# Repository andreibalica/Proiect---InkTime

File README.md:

# InkTime Smartwatch - Documentatie Hardware

Acest repository contine fisierele de proiectare hardware (scheme electronice, layout PCB) pentru InkTime, un smartwatch open-source. Proiectul este axat pe eficientizarea consumului energetic si integrarea unui afisaj bi-stabil.

## 1. Principiu de Functionare si Eficienta Energetica

Sistemul elimina limitarile de autonomie specifice smartwatch-urilor clasice prin utilizarea unui ecran tip E-Paper (electroforetic). 

Datorita proprietatii de bi-stabilitate, matricea display-ului isi pastreaza starea fara a necesita alimentare continua. Consumul de energie are loc exclusiv pe durata ciclului de refresh (schimbarea informatiei afisate). Aceasta caracteristica tehnica permite microcontroller-ului sa ramana in modul "Deep Sleep" pe perioade lungi, asigurand o autonomie extinsa si eliminand totodata necesitatea iluminarii de fundal (Backlight).

## 2. Subsisteme Componente

Arhitectura sistemului este impartita in urmatoarele blocuri functionale majore:

* **Microcontroller (MCU):** Implementat in jurul SoC-ului nRF52840 (Nordic Semiconductor). Ofera suport nativ pentru protocolul Bluetooth 5.0 (BLE) si asigura procesarea generala, gestionand atat magistralele de date, cat si modurile de operare ultra-low power.
* **Power Management Unit (PMU):**
  * **Circuit de Incarcare:** Controller dedicat pe portul USB-C, echipat cu protectie la supratensiune si descarcari electrostatice (ESD / diode TVS).
  * **Regulator DC/DC:** Ofera o tensiune stabilizata de 3.3V necesara liniilor digitale, compensand variatiile de tensiune ale acumulatorului LiPo.
  * **Fuel Gauge:** Integrat de masurare a capacitatii reziduale (State of Charge). Citeste datele celulei LiPo fara a necesita un rezistor de shunt si raporteaza valorile prin I2C.
* **Senzoristica si Interfata Utilizator:**
  * **IMU (Inertial Measurement Unit):** Senzor accelerometric utilizat pentru numararea pasilor si detectia gestului de activare a ecranului.
  * **Driver Haptic:** Asigura comanda prin PWM a motorului de vibratii pentru generarea alertelor tactile.
  * **Input Hardware:** Trei butoane mecanice conectate pe porturile GPIO pentru operarea dispozitivului.

## 3. Interfete de Comunicatie

Comunicatia in interiorul sistemului este structurata pentru a separa transferul de date rapid de citirea senzorilor:

* **Magistrala SPI:** Alocata strict modulului E-Paper. Faciliteaza transferul rapid de date catre controller-ul de display pe parcursul refresh-ului.
* **Magistrala I2C:** Utilizata ca port comun de comunicatie pentru senzorul IMU, integratul Fuel Gauge si driver-ul haptic.
* **Semnale EXTI (Intreruperi):** Butoanele mecanice si pinul de interrupt al senzorului IMU trezesc in mod direct microcontroller-ul din starea de repaus atunci cand se inregistreaza un eveniment fizic.

## 4. Note de Fabricatie si Asamblare (PCBA)

Acest repository include fisierele de productie (Gerber / Pick and Place) si lista de materiale (BOM) necesare pentru fabricarea placii. Pentru a garanta functionarea la parametri optimi a ansamblului, procesul de productie trebuie sa respecte urmatoarele cerinte tehnice:

* **Grosime Substrat:** Placa de baza (PCB) trebuie fabricata cu o grosime stricta de 1.0mm. Utilizarea grosimii standard de 1.6mm va compromite asamblarea mecanica in interiorul carcasei printate 3D.
* **Optimizare PCBA:** Designul a fost conceput pentru a facilita productia automatizata. Toate componentele SMD sunt plasate exclusiv pe stratul superior (TOP Layer), reducand atat complexitatea, cat si costurile procesului de asamblare.
* **Integritate RF si Rutare:** S-a implementat tehnica de "via stitching" intre planurile de masa (TOP si BOTTOM) in vecinatatea circuitului radio. Acest detaliu este critic pentru performanta antenei ceramice la 2.4GHz. De asemenea, erorile de tip "Board Outline Clearance" din zona antenei sunt intentionate, antena necesitand lipsa totala a cuprului pe layerele adiacente.

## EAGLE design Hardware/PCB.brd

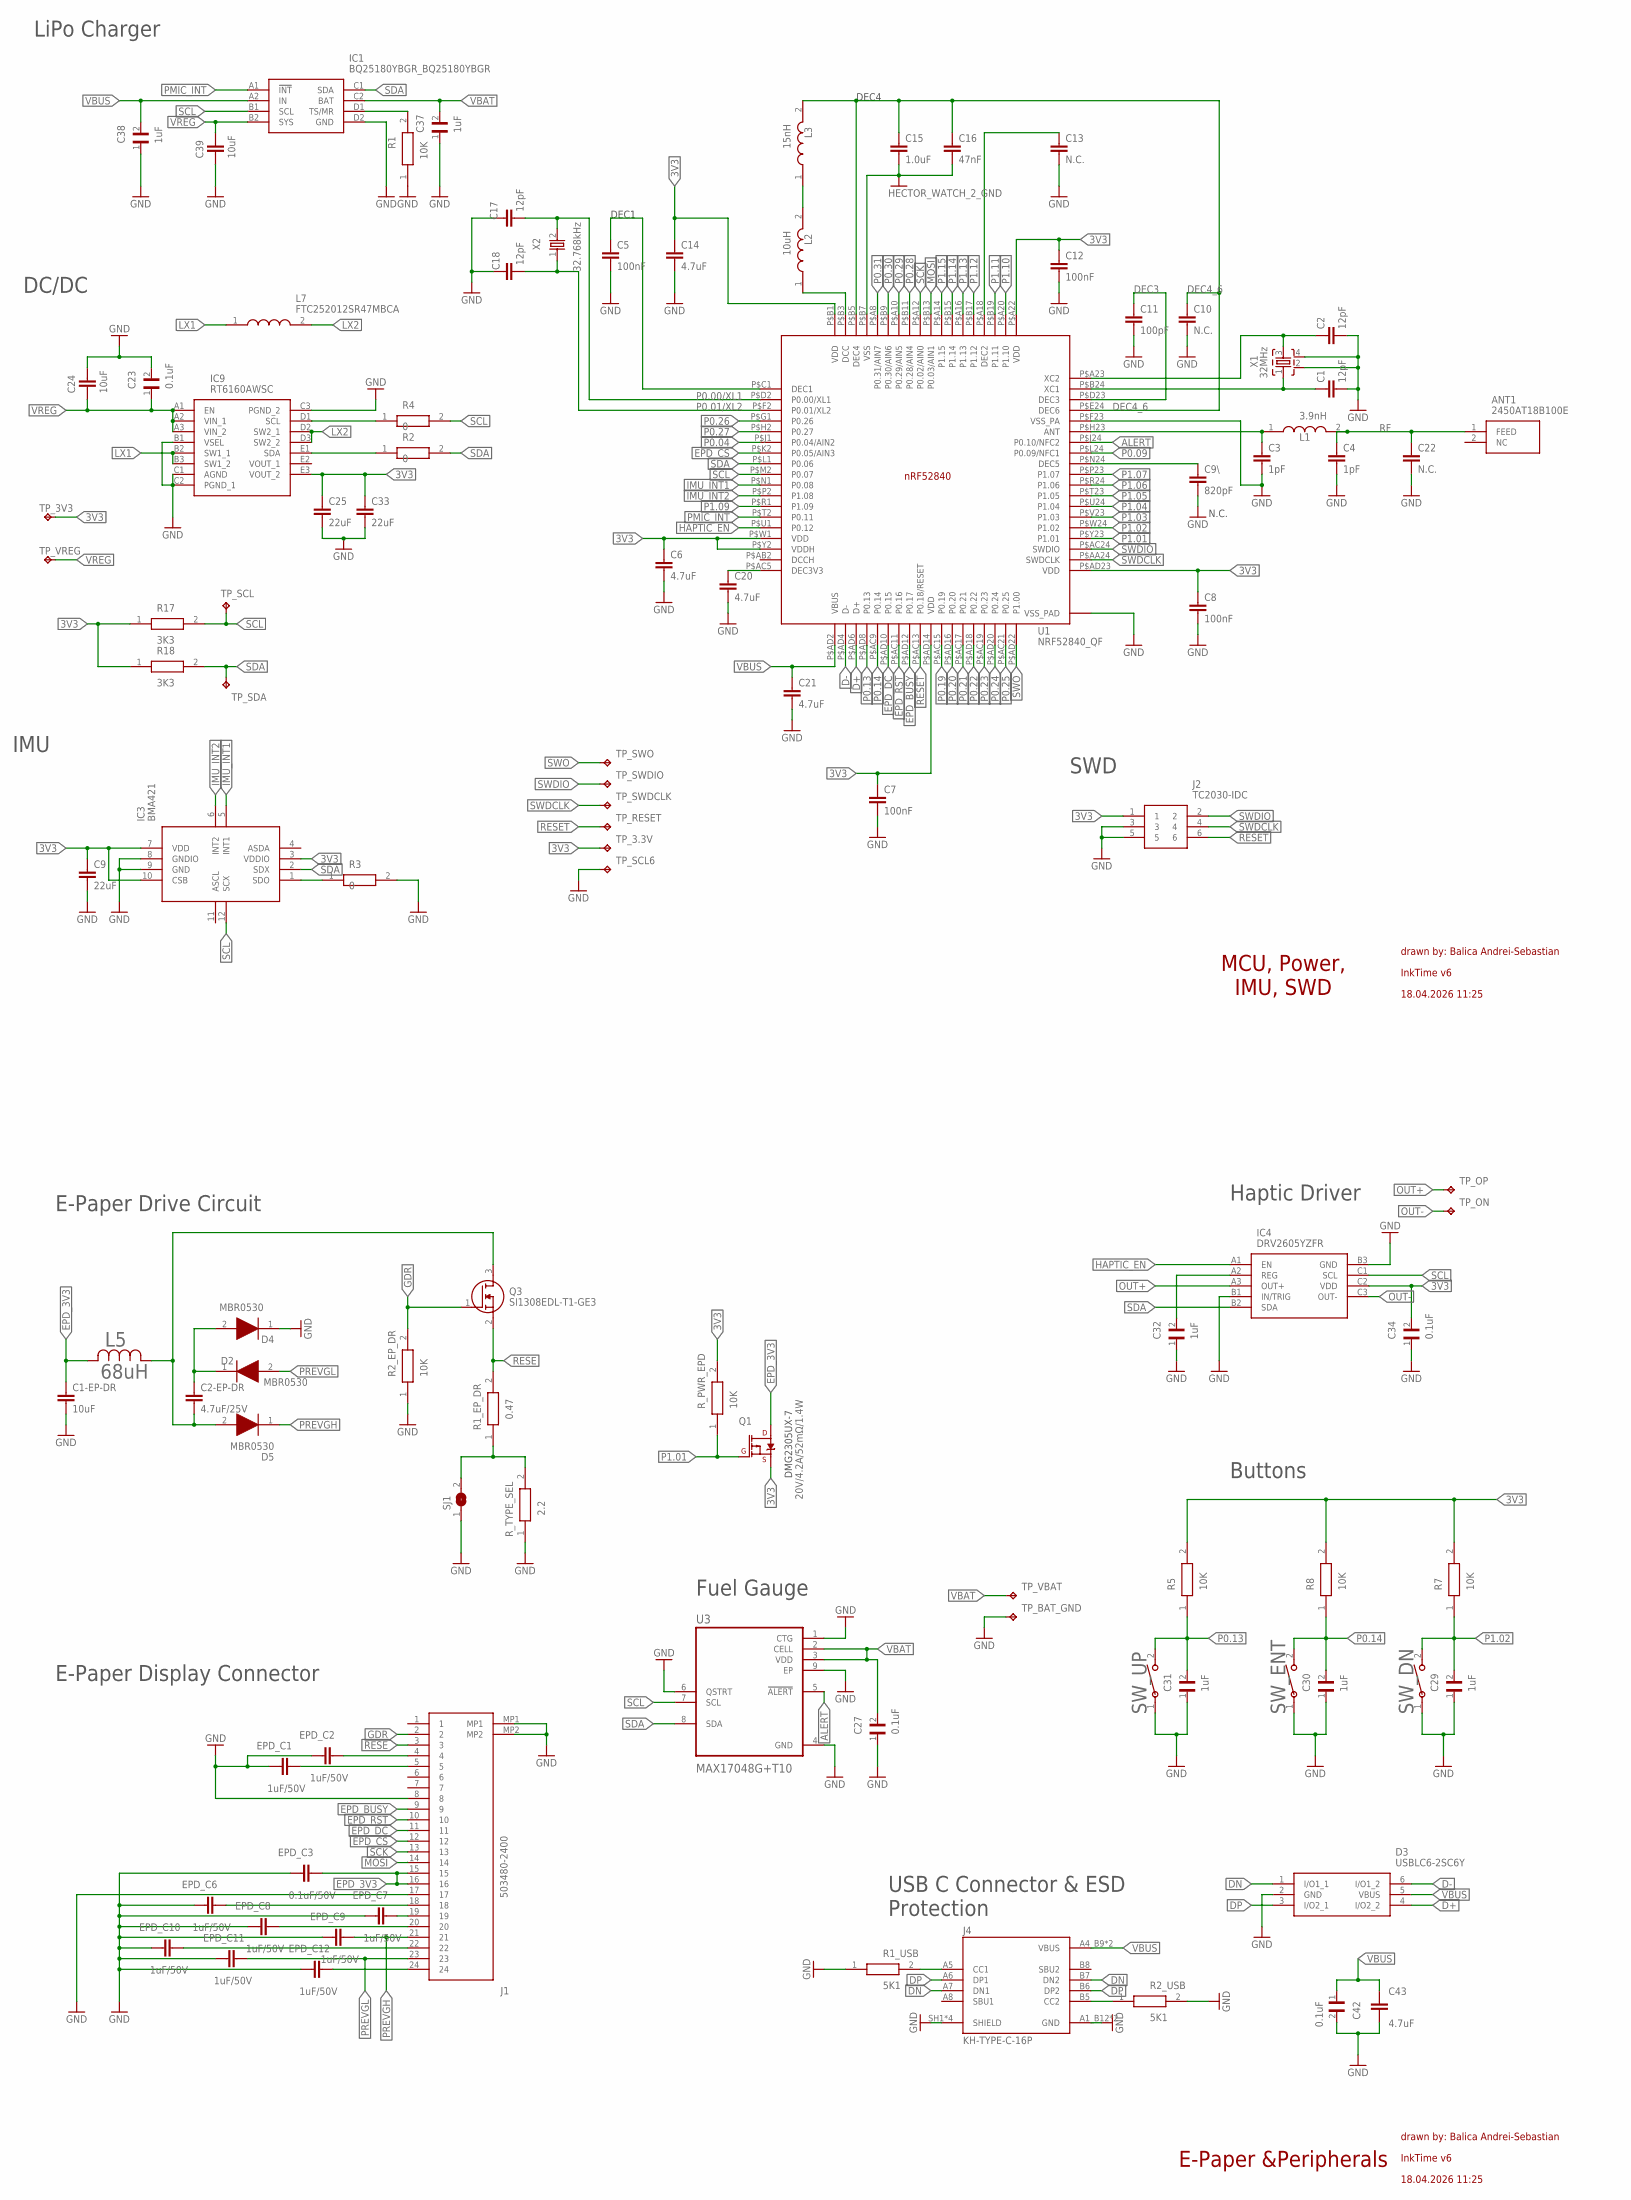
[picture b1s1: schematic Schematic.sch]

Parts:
ANT1: 2450AT18B100E; 2450AT18B100E_ANTC3216X140N
C1, C2, C17, C18: 12pF; NORDIC_NRF_3_RESC0201_L
C1-EP-DR, C24, C39: 10uF; NORDIC_NRF_3_RESC0201_L
C2-EP-DR: 4.7uF/25V; NORDIC_NRF_3_RESC0201_L
C3, C4: 1pF; NORDIC_NRF_3_RESC0201_L
C5, C7, C8, C12: 100nF; NORDIC_NRF_3_RESC0201_L
C6, C14, C20, C21, C43: 4.7uF; NORDIC_NRF_3_RESC0201_L
C9, C25, C33: 22uF; NORDIC_NRF_3_RESC0201_L
C9\: 820pF; NORDIC_NRF_3_RESC0201_L
C10, C13, C22: N.C.; NORDIC_NRF_3_RESC0201_L
C11: 100pF; NORDIC_NRF_3_RESC0201_L
C15: 1.0uF; NORDIC_NRF_3_RESC0201_L
C16: 47nF; NORDIC_NRF_3_RESC0201_L
C23, C27, C34, C42: 0.1uF; GRM011R60J152KE01L_2_CAPC0201X13N
C29, C30, C31, C32, C37, C38: 1uF; GRM011R60J152KE01L_2_CAPC0201X13N
D2, D4, D5: MBR0530; ESP32_C6_LIBRARY_5_SOD3716X135N
D3: USBLC6-2SC6Y; ESP32_C6_LIBRARY_3_SOT95P280X145-6N
EPD_C1, EPD_C2, EPD_C6, EPD_C7, EPD_C8, EPD_C9, EPD_C10, EPD_C11, EPD_C12: 1uF/50V; NORDIC_NRF_3_RESC0201_L
EPD_C3: 0.1uF/50V; NORDIC_NRF_3_RESC0201_L
IC1: BQ25180YBGR_BQ25180YBGR; BQ25180YBGR_BGA8C40P2X4_100X155X50
IC3: BMA421; BMA423_BMA423
IC4: DRV2605YZFR; DRV2605YZFR_BGA9C50P3X3_144X144X62
IC9: RT6160AWSC; RT6160AWSC_BGA15C40P3X5_140X230X60
J1: 503480-2400; 503480-2400_5034802400
J2: TC2030-IDC; TC2030-IDC_TC2030IDC
J4: KH-TYPE-C-16P; KH-TYPE-C-16P_KINGHELM_KH-TYPE-C-16P
L1: 3.9nH; MLP2016SR47MT0S1_INDC2016X100N
L2: 10uH; MLP2016SR47MT0S1_INDC2016X100N
L3: 15nH; MLP2016SR47MT0S1_INDC2016X100N
L5: 68uH; ESP32_C6_LIBRARY_2_IND_4828-WE-TPC_WRE
L7: FTC252012SR47MBCA; MLP2016SR47MT0S1_INDC2016X100N
Q1: 20V/4.2A/52mΩ/1.4W; ESP32_C6_LIBRARY_4_ESP32_C6_LIBRARY_4_ESP32_C6_LIBRARY_4_ES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
Q3: SI1308EDL-T1-GE3; ESP32_C6_LIBRARY_6_SOT65P210X110-3N
R1, R2_EP_DR, R5, R7, R8: 10K; ERA-1AEB3401C_0201
R1_EP_DR: 0.47; ERA-1AEB3401C_0201
R1_USB, R2_USB: 5K1; ERA-1AEB3401C_0201
R2, R3, R4: 0; ERA-1AEB3401C_0201
R17, R18: 3K3; ERA-1AEB3401C_0201
R_PWR_EPD: 10K; ERA-1AEB3401C_0201
R_TYPE_SEL: 2.2; ERA-1AEB3401C_0201
SJ1: ESP32_C6_LIBRARY_7_JUMPER_SJ
SW_DN: 2025-10-22_07-23-44_LIBRARY_EVP-AKE31ASW_EVP-AKE3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; 2025-10-22_07-23-44_LIBRARY_SW_EVP-AKE31A_PAN
SW_ENT: 2025-10-22_07-23-44_LIBRARY_EVP-AKE31ASW_EVP-AKE3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; 2025-10-22_07-23-44_LIBRARY_SW_EVP-AKE31A_PAN
SW_UP: 2025-10-22_07-23-44_LIBRARY_EVP-AKE31ASW_EVP-AKE3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; 2025-10-22_07-23-44_LIBRARY_SW_EVP-AKE31A_PAN
TP_3.3V, TP_3V3: HECTOR_WATCH_1_TPTP20R; HECTOR_WATCH_1_TP20R
TP_BAT_GND: HECTOR_WATCH_1_TPTP20R; HECTOR_WATCH_1_TP20R
TP_ON: HECTOR_WATCH_1_TPTP20R; HECTOR_WATCH_1_TP20R
TP_OP: HECTOR_WATCH_1_TPTP20R; HECTOR_WATCH_1_TP20R
TP_RESET: HECTOR_WATCH_1_TPTP20R; HECTOR_WATCH_1_TP20R
TP_SCL, TP_SCL6: HECTOR_WATCH_1_TPTP20R; HECTOR_WATCH_1_TP20R
TP_SDA: HECTOR_WATCH_1_TPTP20R; HECTOR_WATCH_1_TP20R
TP_SWDCLK: HECTOR_WATCH_1_TPTP20R; HECTOR_WATCH_1_TP20R
TP_SWDIO: HECTOR_WATCH_1_TPTP20R; HECTOR_WATCH_1_TP20R
TP_SWO: HECTOR_WATCH_1_TPTP20R; HECTOR_WATCH_1_TP20R
TP_VBAT: HECTOR_WATCH_1_TPTP20R; HECTOR_WATCH_1_TP20R
TP_VREG: HECTOR_WATCH_1_TPTP20R; HECTOR_WATCH_1_TP20R
U1: NRF52840_QF; NORDIC_NRF_4_AQFN50P700X700X85_HS-74N
U3: MAX17048G+T10; ESP32_C6_LIBRARY_SON50P200X200X80-9N
X1: 32MHz; NORDIC_NRF_BT-XTAL_2016_N
X2: 32.768kHz; NORDIC_NRF_1_XTAL_3215_N

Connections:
3V3: C6.1, C7.1, C8.1, C9.1, C12.1, C14.1, C25.1, C33.1, C34.2, IC3.3 (VDDIO), IC3.7 (VDD), IC3.10 (CSB), IC4.C2 (VDD), IC9.E3 (VOUT_2), J2.1, Q1.2 (S), R5.2, R7.2, R8.2, R17.1, R18.1, R_PWR_EPD.2, TP_3.3V.TP, TP_3V3.TP, U1.P$A22 (VDD), U1.P$AD14 (VDD), U1.P$AD23 (VDD), U1.P$B1 (VDD), U1.P$W1 (VDD), U1.P$Y2 (VDDH)
ALERT: U1.P$J24 (P0.10/NFC2), U3.5 (!ALERT)
D+: D3.4 (I/O2_2), U1.P$AD6 (D+)
D-: D3.6 (I/O1_2), U1.P$AD4 (D-)
DEC3: C11.1, U1.P$D23 (DEC3)
DEC4_6: C10.1, C15.1, C16.1, L3.2, U1.P$B5 (DEC4), U1.P$E24 (DEC6)
DN: D3.1 (I/O1_1), J4.A7 (DN1), J4.B7 (DN2)
DP: D3.3 (I/O2_1), J4.A6 (DP1), J4.B6 (DP2)
EPD_3V3: C1-EP-DR.1, EPD_C3.2, J1.15, J1.16, L5.2, Q1.3 (D)
EPD_BUSY: J1.9, U1.P$AD12 (P0.17)
EPD_CS: J1.12, U1.P$K2 (P0.05/AIN3)
EPD_DC: J1.11, U1.P$AD10 (P0.15)
EPD_RST: J1.10, U1.P$AC11 (P0.16)
GDR: J1.2, Q3.1 (G), R2_EP_DR.2
GND: C1.2, C1-EP-DR.2, C2.2, C3.2, C4.2, C5.2, C6.2, C7.2, C8.2, C9.2, C9\.2, C10.2, C11.2, C12.2, C13.2, C14.2, C15.2, C16.2, C17.1, C18.2, C20.2, C21.2, C22.2, C23.2, C24.1, C25.2, C27.1, C29.1, C30.1, C31.1, C32.1, C33.2, C34.1, C37.1, C38.1, C39.2, C42.2, C43.2, D3.2 (GND), D4.1 (K), EPD_C1.1, EPD_C2.1, EPD_C3.1, EPD_C6.1, EPD_C7.1, EPD_C8.1, EPD_C9.1, EPD_C10.1, EPD_C11.1, EPD_C12.1, IC1.D2 (GND), IC3.8 (GNDIO), IC3.9 (GND), IC4.B1 (IN/TRIG), IC4.B3 (GND), IC9.B1 (VSEL), IC9.C1 (AGND), IC9.C2 (PGND_1), IC9.C3 (PGND_2), J1.8, J1.17, J1.MP1, J1.MP2, J2.3, J2.5, J4.A1_B12 (GND), J4.A12_B1 (GND), J4.SH1 (SHIELD), J4.SH2 (SHIELD), J4.SH3 (SHIELD), J4.SH4 (SHIELD), R1.1, R1_USB.1, R2_EP_DR.1, R2_USB.2, R3.2, R_TYPE_SEL.1, SJ1.1, SW_DN.1, SW_ENT.1, SW_UP.1, TP_BAT_GND.TP, TP_SCL6.TP, U1.P$74 (VSS_PAD), U1.P$75 (VSS_PAD), U1.P$76 (VSS_PAD), U1.P$77 (VSS_PAD), U1.P$78 (VSS_PAD), U1.P$79 (VSS_PAD), U1.P$80 (VSS_PAD), U1.P$81 (VSS_PAD), U1.P$82 (VSS_PAD), U1.P$83 (VSS_PAD), U1.P$84 (VSS_PAD), U1.P$85 (VSS_PAD), U1.P$86 (VSS_PAD), U1.P$87 (VSS_PAD), U1.P$88 (VSS_PAD), U1.P$89 (VSS_PAD), U1.P$90 (VSS_PAD), U1.P$B7 (VSS), U1.P$F23 (VSS_PA), U3.1 (CTG), U3.4 (GND), U3.6 (QSTRT), U3.9 (EP), X1.2, X1.4
HAPTIC_EN: IC4.A1 (EN), U1.P$U1 (P0.12)
IMU_INT1: IC3.5 (INT1), U1.P$N1 (P0.08)
IMU_INT2: IC3.6 (INT2), U1.P$P2 (P1.08)
LX1: IC9.B2 (SW1_1), IC9.B3 (SW1_2), L7.1
LX2: IC9.D2 (SW2_1), IC9.D3 (SW2_2), L7.2
MOSI: J1.14, U1.P$B13 (P0.03/AIN1)
unnamed: C13.1, U1.P$A18 (DEC2)
unnamed: C5.1, U1.P$C1 (DEC1)
unnamed: IC1.D1 (TS/MR), R1.2
unnamed: IC9.D1 (SCL), R4.1
unnamed: IC9.E1 (SDA), R2.1
unnamed: L2.1, U1.P$B3 (DCC)
unnamed: L2.2, L3.1
unnamed: C20.1, U1.P$AC5 (DEC3V3)
unnamed: C3.1, L1.1, U1.P$H23 (ANT)
unnamed: C9\.1, U1.P$N24 (DEC5)
unnamed: C2.1, U1.P$A23 (XC2), X1.3
unnamed: C1.1, U1.P$B24 (XC1), X1.1
unnamed: C18.1, U1.P$F2 (P0.01/XL2), X2.1
unnamed: C2-EP-DR.2, D5.2 (A), L5.1, Q3.3 (D)
unnamed: C2-EP-DR.1, D2.1 (K), D4.2 (A)
unnamed: EPD_C2.2, J1.4
unnamed: EPD_C6.2, J1.18
unnamed: R1_EP_DR.1, R_TYPE_SEL.2, SJ1.2
unnamed: IC3.1 (SDO), R3.1
unnamed: EPD_C1.2, J1.5
unnamed: EPD_C7.2, J1.19
unnamed: EPD_C8.2, J1.20
unnamed: EPD_C10.2, J1.22
unnamed: EPD_C12.2, J1.24
unnamed: C32.2, IC4.A2 (REG)
unnamed: J4.A5 (CC1), R1_USB.2
unnamed: J4.B5 (CC2), R2_USB.1
OUT+: IC4.A3 (OUT+), TP_OP.TP
OUT-: IC4.C3 (OUT-), TP_ON.TP
P0.00/XL1: C17.2, U1.P$D2 (P0.00/XL1), X2.2
P0.04: U1.P$J1 (P0.04/AIN2)
P0.09: U1.P$L24 (P0.09/NFC1)
P0.13: C31.2, R5.1, SW_UP.2, U1.P$AD8 (P0.13)
P0.14: C30.2, R8.1, SW_ENT.2, U1.P$AC9 (P0.14)
P0.19: U1.P$AC15 (P0.19)
P0.20: U1.P$AD16 (P0.20)
P0.21: U1.P$AC17 (P0.21)
P0.22: U1.P$AD18 (P0.22)
P0.23: U1.P$AC19 (P0.23)
P0.24: U1.P$AD20 (P0.24)
P0.25: U1.P$AC21 (P0.25)
P0.26: U1.P$G1 (P0.26)
P0.27: U1.P$H2 (P0.27)
P0.28: U1.P$B11 (P0.28/AIN4)
P0.29: U1.P$A10 (P0.29/AIN5)
P0.30: U1.P$B9 (P0.30/AIN6)
P0.31: U1.P$A8 (P0.31/AIN7)
P1.01: Q1.1 (G), R_PWR_EPD.1, U1.P$Y23 (P1.01)
P1.02: C29.2, R7.1, SW_DN.2, U1.P$W24 (P1.02)
P1.03: U1.P$V23 (P1.03)
P1.04: U1.P$U24 (P1.04)
P1.05: U1.P$T23 (P1.05)
P1.06: U1.P$R24 (P1.06)
P1.07: U1.P$P23 (P1.07)
P1.09: U1.P$R1 (P1.09)
P1.10: U1.P$A20 (P1.10)
P1.11: U1.P$B19 (P1.11)
P1.12: U1.P$B17 (P1.12)
P1.13: U1.P$A16 (P1.13)
P1.14: U1.P$B15 (P1.14)
P1.15: U1.P$A14 (P1.15)
PMIC_INT: IC1.A1 (!INT), U1.P$T2 (P0.11)
PREVGH: D5.1 (K), EPD_C9.2, J1.21
PREVGL: D2.2 (A), EPD_C11.2, J1.23
RESE: J1.3, Q3.2 (S), R1_EP_DR.2
RESET: J2.6, TP_RESET.TP, U1.P$AC13 (P0.18/RESET)
RF: ANT1.1 (FEED), C4.1, C22.1, L1.2
SCK: J1.13, U1.P$A12 (P0.02/AIN0)
SCL: IC1.B1 (SCL), IC3.12 (SCX), IC4.C1 (SCL), R4.2, R17.2, TP_SCL.TP, U1.P$M2 (P0.07), U3.7 (SCL)
SDA: IC1.C1 (SDA), IC3.2 (SDX), IC4.B2 (SDA), R2.2, R18.2, TP_SDA.TP, U1.P$L1 (P0.06), U3.8 (SDA)
SWDCLK: J2.4, TP_SWDCLK.TP, U1.P$AA24 (SWDCLK)
SWDIO: J2.2, TP_SWDIO.TP, U1.P$AC24 (SWDIO)
SWO: TP_SWO.TP, U1.P$AD22 (P1.00)
VBAT: C27.2, C37.2, IC1.C2 (BAT), TP_VBAT.TP, U3.2 (CELL), U3.3 (VDD)
VBUS: C21.1, C38.2, C42.1, C43.1, D3.5 (VBUS), IC1.A2 (IN), J4.A4_B9 (VBUS), J4.A9_B4 (VBUS), U1.P$AD2 (VBUS)
VREG: C23.1, C24.2, C39.1, IC1.B2 (SYS), IC9.A1 (EN), IC9.A2 (VIN_1), IC9.A3 (VIN_2), TP_VREG.TP

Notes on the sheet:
LiPo Charger
DC/DC
DEC1
DEC4
N.C.
IMU
SWD
E-Paper Drive Circuit
E-Paper Display Connector
DMG2305UX-7
Fuel Gauge
Haptic Driver
Buttons
USB C Connector & ESD Protection
E-Paper &Peripherals
drawn by: Balica Andrei-Sebastian
InkTime v6
18.04.2026 11:25
MCU, Power, IMU, SWD

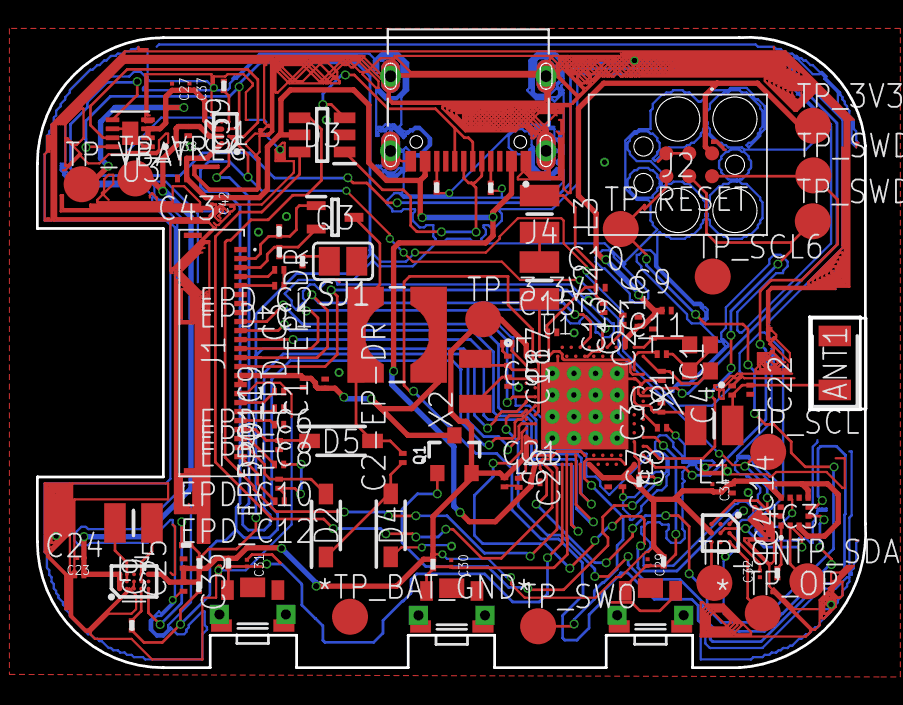
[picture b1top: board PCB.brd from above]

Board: 2 copper layers, 46.0 x 35.0 mm, 105 parts (0 on the bottom side), 70 nets.

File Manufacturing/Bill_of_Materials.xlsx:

Name | Proiect
Exported by | andrei.balica@stud.acs.upb.ro
Time of Export | 20/04/2026 14:44
Reference Designators | Quantity | Description | Package | Value | Manufacturer | Manufacturer Part Number | Vendor | Vendor Part Number | Top/Bottom
 | 1 | PCB Board | Board
ANT1 | 1 | Antennas 2.45GHz ANTENNA | 2450AT18B100E_ANTC3216X140N | 2450AT18B100E |  |  |  |  | Top
C1, C2, C17, C18 | 4 | Generic chip capacitor | NORDIC_NRF_3_RESC0201_L | 12pF |  |  |  |  | Top
C1-EP-DR, C24, C39 | 3 | Generic chip capacitor | NORDIC_NRF_3_RESC0201_L | 10uF |  |  |  |  | Top
C2-EP-DR | 1 | Generic chip capacitor | NORDIC_NRF_3_RESC0201_L | 4.7uF/25V |  |  |  |  | Top
C3, C4 | 2 | Generic chip capacitor | NORDIC_NRF_3_RESC0201_L | 1pF |  |  |  |  | Top
C5, C7, C8, C12 | 4 | Generic chip capacitor | NORDIC_NRF_3_RESC0201_L | 100nF |  |  |  |  | Top
C6, C14, C20, C21, C43 | 5 | Generic chip capacitor | NORDIC_NRF_3_RESC0201_L | 4.7uF |  |  |  |  | Top
C9, C25, C33 | 3 | Generic chip capacitor | NORDIC_NRF_3_RESC0201_L | 22uF |  |  |  |  | Top
C9\ | 1 | Generic chip capacitor | NORDIC_NRF_3_RESC0201_L | 820pF |  |  |  |  | Top
C10, C13, C22 | 3 | Generic chip capacitor | NORDIC_NRF_3_RESC0201_L | N.C. |  |  |  |  | Top
C11 | 1 | Generic chip capacitor | NORDIC_NRF_3_RESC0201_L | 100pF |  |  |  |  | Top
C15 | 1 | Generic chip capacitor | NORDIC_NRF_3_RESC0201_L | 1.0uF |  |  |  |  | Top
C16 | 1 | Generic chip capacitor | NORDIC_NRF_3_RESC0201_L | 47nF |  |  |  |  | Top
C23, C27, C34, C42 | 4 | Check availability | CAPC0201X13N | 0.1uF |  |  |  |  | Top
C29, C30, C31, C32, C37, C38 | 6 | Check availability | CAPC0201X13N | 1uF |  |  |  |  | Top
D2, D4, D5 | 3 | ON SEMICONDUCTOR - MBR0530 - DIODE, SCHOTTKY, 0.5A, 30V, SOD-123 | SOD3716X135N | MBR0530 |  |  |  |  | Top
D3 | 1 | Low Cap. ESD Protection Auto SOT-23-6 STMicroelectronics USBLC6-2SC6Y, Dual Uni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 | SOT95P280X145-6N | USBLC6-2SC6Y |  |  |  |  | Top
EPD_C1, EPD_C2, EPD_C6, EPD_C7, EPD_C8, EPD_C9, EPD_C10, EPD_C11, EPD_C12 | 9 | Generic chip capacitor | NORDIC_NRF_3_RESC0201_L | 1uF/50V |  |  |  |  | Top
EPD_C3 | 1 | Generic chip capacitor | NORDIC_NRF_3_RESC0201_L | 0.1uF/50V |  |  |  |  | Top
IC1 | 1 | Charger IC Lithium Ion/Polymer, Lithium Iron Phosphate 8-DSBGA (1.6x1.1) | BQ25180YBGR_BGA8C40P2X4_100X155X50 | BQ25180YBGR_BQ25180YBGR |  |  |  |  | Top
IC3 | 1 | Accelerometers Triaxial low-g 12bit Acceleration Sensor | BMA423_BMA423 | BMA421 |  |  |  |  | Top
IC4 | 1 | Haptic Driver for ERM/LRA with Built-In Library and Smart Loop Architecture | DRV2605YZFR_BGA9C50P3X3_144X144X62 | DRV2605YZFR |  |  |  |  | Top
IC9 | 1 | Buck-Boost Regulator Positive Output Step-Up/Step-Down I2C DC-DC Controller IC 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 | RT6160AWSC_BGA15C40P3X5_140X230X60 | RT6160AWSC |  |  |  |  | Top
J1 | 1 | FFC & FPC Connectors 0.5mm FPC RA SMT Dual Contact 24Ckt | 503480-2400_5034802400 | 503480-2400 |  |  |  |  | Top
J2 | 1 | CABLE ADAPTER 6 POS | TC2030-IDC_TC2030IDC | TC2030-IDC |  |  |  |  | Top
J4 | 1 | Check availability | KINGHELM_KH-TYPE-C-16P | KH-TYPE-C-16P |  |  |  |  | Top
L1 | 1 | SMD / SMT Inductors (Coils), L=0.47?H, L x W x T : | MLP2016SR47MT0S1_INDC2016X100N | 3.9nH |  |  |  |  | Top
L2 | 1 | SMD / SMT Inductors (Coils), L=0.47?H, L x W x T : | MLP2016SR47MT0S1_INDC2016X100N | 10uH |  |  |  |  | Top
L3 | 1 | SMD / SMT Inductors (Coils), L=0.47?H, L x W x T : | MLP2016SR47MT0S1_INDC2016X100N | 15nH |  |  |  |  | Top
L5 | 1 |  | ESP32_C6_LIBRARY_2_IND_4828-WE-TPC_WRE | 68uH |  |  |  |  | Top
L7 | 1 | SMD / SMT Inductors (Coils), L=0.47?H, L x W x T : | MLP2016SR47MT0S1_INDC2016X100N | FTC252012SR47MBCA |  |  |  |  | Top
Q1 | 1 | P-channel MOSFETs | ESP32_WROVER_SPARKFUN-DISCRETESEMI_SOT23-3 | 20V/4.2A/52mΩ/1.4W |  |  |  |  | Top
Q3 | 1 | MOSFET N-Ch 30V 1.5A TrenchFET SC70 Vishay Si1308EDL-T1-GE3 N-channel MOSFET Tr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 | SOT65P210X110-3N | SI1308EDL-T1-GE3 |  |  |  |  | Top
R_PWR_EPD, R1, R2_EP_DR, R5, R7, R8 | 6 | 7.68k 0201 Thin Film Surface Mount Fixed Resistor +/-0.5% 0.031W CPF0201D7K68C1 | R0201 | 10K |  |  |  |  | Top
R_TYPE_SEL | 1 | 7.68k 0201 Thin Film Surface Mount Fixed Resistor +/-0.5% 0.031W CPF0201D7K68C1 | R0201 | 2.2000000000000002 |  |  |  |  | Top
R1_EP_DR | 1 | 7.68k 0201 Thin Film Surface Mount Fixed Resistor +/-0.5% 0.031W CPF0201D7K68C1 | R0201 | 0.46999999999999997 |  |  |  |  | Top
R1_USB, R2_USB | 2 | 7.68k 0201 Thin Film Surface Mount Fixed Resistor +/-0.5% 0.031W CPF0201D7K68C1 | R0201 | 5K1 |  |  |  |  | Top
R2, R3, R4 | 3 | 7.68k 0201 Thin Film Surface Mount Fixed Resistor +/-0.5% 0.031W CPF0201D7K68C1 | R0201 | 0 |  |  |  |  | Top
R17, R18 | 2 | 7.68k 0201 Thin Film Surface Mount Fixed Resistor +/-0.5% 0.031W CPF0201D7K68C1 | R0201 | 3K3 |  |  |  |  | Top
SJ1 | 1 | SMD solder JUMPER | JUMPER_SJ |  |  |  |  |  | Top
SW_DN, SW_ENT, SW_UP | 3 |  | SW_EVP-AKE31A_PAN | 2025-10-22_07-23-44_LIBRARY_EVP-AKE31ASW_EVP-AKE31A_PAN |  |  |  |  | Top
TP_3.3V, TP_3V3, TP_BAT_GND, TP_ON, TP_OP, TP_RESET, TP_SCL, TP_SCL6, TP_SDA, T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 | 14 | Test pad | HECTOR_WATCH_1_TP20R | HECTOR_WATCH_1_TPTP20R |  |  |  |  | Top
U1 | 1 | nRF52840 | NORDIC_NRF_4_AQFN50P700X700X85_HS-74N | NRF52840_QF |  |  |  |  | Top
U3 | 1 | Check availability | SON50P200X200X80-9N | MAX17048G+T10 |  |  |  |  | Top
X1 | 1 |  | NORDIC_NRF_BT-XTAL_2016_N | 32MHz |  |  |  |  | Top
X2 | 1 |  | NORDIC_NRF_1_XTAL_3215_N | 32.768kHz |  |  |  |  | Top

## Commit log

2026-04-10 First stage
2026-04-20 Final Project

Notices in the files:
parts and their libraries:
COPYRIGHT: Copyright (C) 2024 Ultra Librarian. All rights reserved.
COPYRIGHT: Copyright (C) 2025 Ultra Librarian. All rights reserved.
